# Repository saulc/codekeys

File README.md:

# codekeys
 arduino based mini mech keyboard

<br />This work is licensed under a <a rel="license" href="http://creativecommons.org/licenses/by-nc-sa/4.0/">Creative Commons Attribution-NonCommercial-ShareAlike 4.0 International License</a>.

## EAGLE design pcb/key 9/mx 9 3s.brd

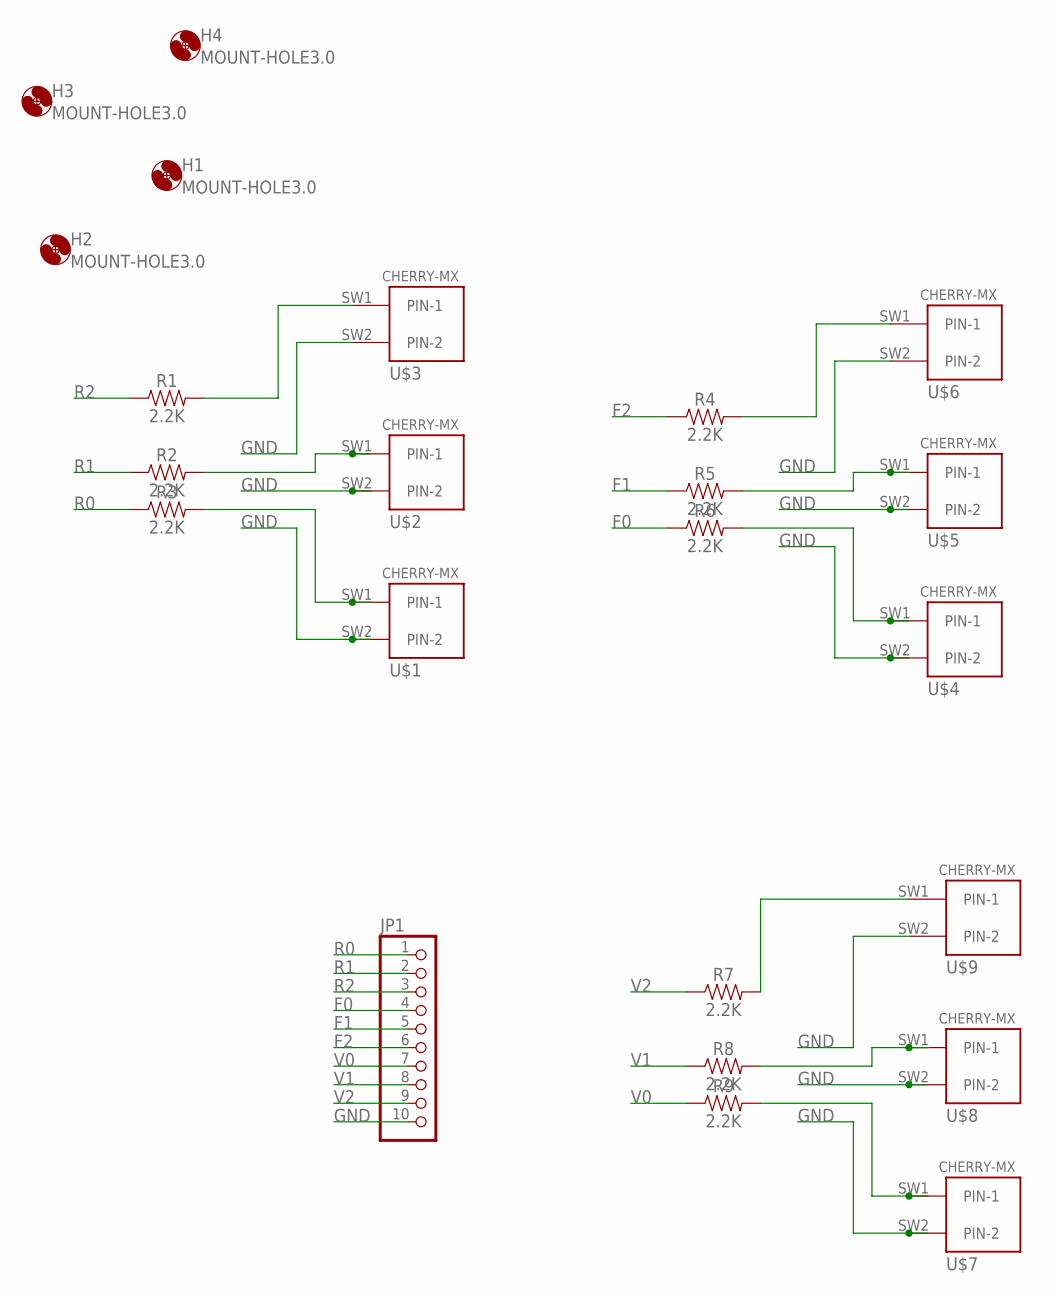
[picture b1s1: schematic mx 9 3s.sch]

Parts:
H1, H2, H3, H4: MOUNT-HOLE3.0; 3,0
JP1: PINHD-1X10; 1X10
R1, R2, R3, R4, R5, R6, R7, R8, R9: 2.2K; 0402
U$1, U$2, U$3, U$4, U$5, U$6, U$7, U$8, U$9: CHERRY-MX

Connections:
F0: JP1.4, R6.1
F1: JP1.5, R5.1
F2: JP1.6, R4.1
GND: JP1.10, U$1.SW2 (PIN-2), U$2.SW2 (PIN-2), U$3.SW2 (PIN-2), U$4.SW2 (PIN-2), U$5.SW2 (PIN-2), U$6.SW2 (PIN-2), U$7.SW2 (PIN-2), U$8.SW2 (PIN-2), U$9.SW2 (PIN-2)
K0: R3.2, U$1.SW1 (PIN-1)
K1: R2.2, U$2.SW1 (PIN-1)
K2: R1.2, U$3.SW1 (PIN-1)
K3: R4.2, U$6.SW1 (PIN-1)
K4: R5.2, U$5.SW1 (PIN-1)
K5: R6.2, U$4.SW1 (PIN-1)
K6: R7.2, U$9.SW1 (PIN-1)
K7: R8.2, U$8.SW1 (PIN-1)
K8: R9.2, U$7.SW1 (PIN-1)
R0: JP1.1, R3.1
R1: JP1.2, R2.1
R2: JP1.3, R1.1
V0: JP1.7, R9.1
V1: JP1.8, R8.1
V2: JP1.9, R7.1

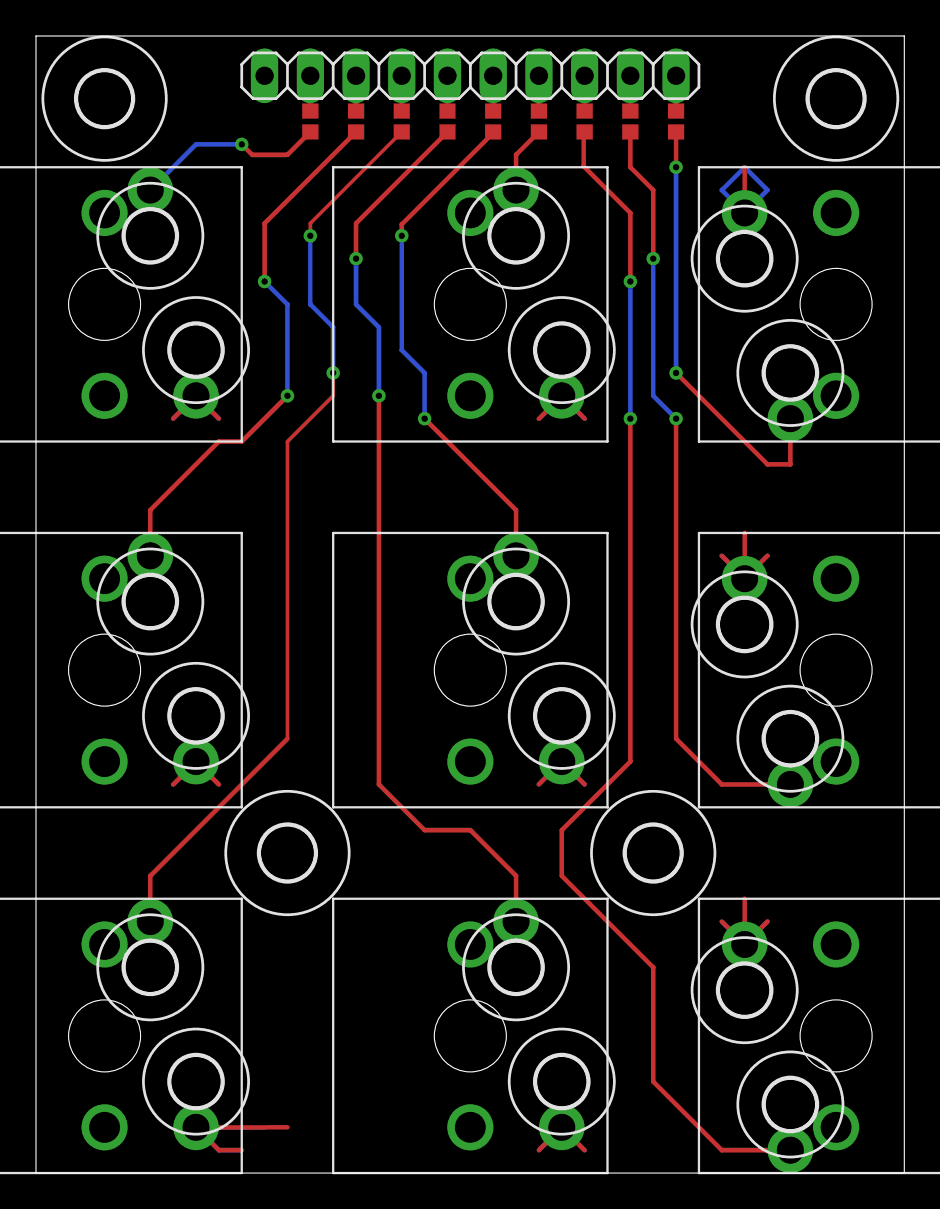
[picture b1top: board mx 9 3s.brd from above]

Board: 2 copper layers, 48.2 x 63.2 mm, 23 parts (0 on the bottom side), 19 nets.

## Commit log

2022-08-04 basic sketch
    90 lines....
    does it really need more?
2022-08-04 doubletap
    what rule was that?
2022-08-04 difference short cuts
    is 3 keys enough?
2022-08-05 3x3
    i guess 10x keys is possible?
    adding pcint buttons
2022-08-05 9 buttons!
    micro doesn't have a pin 11. or 12..
2022-08-06 clean up
    ...
2022-08-07 added license
    ..
2022-08-07 update
    readme
2022-08-07 name change
    mode switch could be interesting...
2022-08-08 comments
    the ks page is live...
2022-08-08 added eagle files
    3x3 v1
2022-08-10 base code
    for software rotate/transpose.
    rotate layout quickly.
    account for alt wiring.
2022-08-12 new config
    editor config,
    tab/ret del
    arrow pad
    copycut/paste/undo
2022-08-12 dt
    editing layout!
2022-08-20 test
    test code/starter code
2022-08-31 wireless
    esp32 v2 feather working with ble keyboard fully wireless....
    needs indicators. led/rgb...
    external reset button? or a hole...
2022-08-31 battery level
    and fixed crash(blocking) issue...
2022-08-31 batt level
    added analog smoothing to batt level and 'active' mode updates.
    fixed sleep/wake issue.?
2023-02-23 batt
    wireless
2025-01-15 update
    just better response

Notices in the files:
parts and their libraries:
SparkFun-Resistors: Licensing: Creative Commons ShareAlike 4.0 International - https://creativecommons.org/licenses/by-sa/4.0
